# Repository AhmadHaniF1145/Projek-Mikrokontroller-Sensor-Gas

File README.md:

Sistem pendeteksi kebocoran gas adalah sistem elektronik yang dirancang untuk mendeteksi dan memberi peringatan tentang kebocoran gas. Peringatan yang dihasilkan adalah dalam bentuk audio sesuai gas yang dideteksi beserta tingkat bahayanya.

`WORKSHOP MIKROKONTROLLER - PROGRAM STUDI TEKNIK ELEKTRONIKA - POLITEKNIK ELEKTRONIKA NEGERI SURABAYA`

`DOSEN PENGAMPU : Akhmad Hendriawan ST, MT`
`NIP. 197501272002121003`

`TEAM`
| No.  | Nama  | NRP  | Pembagian Tugas  |
| :------------: | :------------: | :------------: | :------------: |
| 1  | Ahmad Hanif Abiyyu Khrisna  | 2122500031  | Pengujian Sistem Pada Software, Pengujian Alat  |
| 2  | Nawfal Ulinnuha F  | 2122500041  | Publikasi melalui Github, Pembelian Hardware  |
| 3  |  Clarrisa Fitria A  | 2122500046  |  Studi Literatur, Pembuatan Audio Project |
| 4  |  Fatimah Azzahro |  2122500047 | Publikasi melalui Github, Pembuatan Audio Project |
| 5  |  Muhammad Ilham K | 2122500052  |  Desain 3D, Proses Perakitan dan Soldering, Proses Pemrograman Arduino |
| 6  | Artur Ferdiansyah  |  2122500059 | Desain Skematik dan PCB Board, Proses Perakitan dan Soldering, Proses Pemrograman Arduino  |

## Daftar Isi
- [Komponen Yang Digunakan](#Komponen-Yang-Digunakan)
- [Konsep Simulasi](#Konsep-Simulasi)
- [Skematik Rangkaian](#Skematik-Rangkaian)
- [Informasi Penempatan Modul dan Komponen](#Informasi-Penempatan-Modul-dan-Komponen)
- [Audio Project](#Audio-Project)
- [Proses Pengerjaan](#Proses-Pengerjaan)
- [Hasil](#Hasil)
- [Cara Penggunaan Alat](#Cara-Penggunaan-Alat)

## Komponen Yang Digunakan
1. Arduino Mega 2560
2. Gas Sensor MQ2
3. OLED 0.96 Inch
4. Push Button
5. LED 3mm
6. SMD LED 1206
7. Speaker/Buzzer
8. Modul amplifier PAM8403
9. IC SPI Flash W25Q32JVSSIQ (4MB)

Dan Beberapa komponen pasif seperti resistor yang salah satunya digunakan sebagai pembatas arus pada LED indikator, dan kapasitor yang digunakan pada blok rangkaian SPI Flash Eksternal yang digunakan sebagai penyimpanan data tambahan.

## Blok Diagram

Prinsip kerja dari sistem pendeteksi kebocoran gas yaitu dimulai dengan sistem pertama kali digunakan dimana sumber daya berasal dari baterai. Ketika tidak terdeteksi kebocoran gas, maka LED hijau akan selalu menyala. Ketika kebocoran gas terdeteksi oleh sensor MQ-2 dengan threshold yang telah disetting oleh push button 1, maka speaker mengeluarkan audio. Untuk informasi threshold yaitu threshold 400 dan 600 masih dalam level siaga dengan indikasi audio "terdeteksi kebocoran gas hati-hati siaga", kemudian threshold 800 sudah dalam level bahaya dengan indikasi audio "bahaya, bahaya, bahaya terdeteksi kebocoran gas". LCD OLED digunakan untuk menampilkan informasi threshold dan banyaknya gas yang terdeteksi. Jika gas yang terdeteksi melebihi threshold, maka speaker mengeluarkan audio dibarengi dengan LED merah yang juga ikut menyala. Untuk mematikan speaker, digunakan push button 2 dan LED hijau kembali menyala yang berarti kondisi sudah diatasi atau sudah aman.

## Konsep Simulasi
Berikut adalah skematik breadboard untuk simulasi menggunakan TinkerCad yang menggunakan Arduino Uno.

https://github.com/AhmadHaniF1145/Projek-Mikrokontroller-Sensor-Gas/assets/168633171/c68b0559-28a6-41bc-bea3-4cfa7fe1158b

## Skematik Rangkaian
Berikut ini adalah hasil skematik rangkaian sistem pendeteksi kebocoran gas menggunakan software KiCad.

Berikut adalah link tutorial dalam pembuatan skematik menggunakan KiCad bisa dilihat pada video [berikut.](https://youtu.be/a5kBzt2_dH4 "berikut.") Untuk semua file yang dibutuhkan terkait skematik rangkaian bisa diakses pada link [berikut.](https://github.com/AhmadHaniF1145/Projek-Mikrokontroller-Sensor-Gas/tree/main/PCB%20Board "berikut.")

## Desain 3D
Berikut ini adalah hasil [desain 3D](https://github.com/AhmadHaniF1145/Projek-Mikrokontroller-Sensor-Gas/tree/main/Desain%203D "Desain 3D") :
1. Desain 3D Casing <br>
<br>
2. Desain 3D Casing + Komponen <br>
<br>
3. Desain 3D PCB dengan Komponen <br>
<br>
4. Desain 3D PCB tanpa Komponen <br>
<br>

Berikut adalah video tutorial pembuatan desain casing menggunakan Autodesk Fusion versi sederhana. Klik link [youtube berikut](https://youtu.be/2gopSfegvmg?si=Se-gvMHZY0zX1dgN "youtube berikut")

Berikut adalah tutorial dalam pembuatan desain PCB menggunakan KiCad pada proyek ini. Bisa klik link [berikut.](https://youtu.be/dg8yomkr-xE "berikut.")

Asset 3D yang sudah jadi dapat di download pada [link Thingiverse berikut](https://www.thingiverse.com/thing:6621092 "link Thingiverse berikut")

## Informasi Penempatan Modul dan Komponen
Tata letak dan informasi terkait penempatan Modul dan Komponen untuk memudahkan pengguna dalam melakukan perakitan <br>
<br>

## Manufacture Drawing untuk Casing
Berikut adalah detail ukuran casing untuk kebutuhan manufaktur
<br>

https://github.com/AhmadHaniF1145/Projek-Mikrokontroller-Sensor-Gas/assets/91182185/3b76fa04-874f-4a73-a389-29a3c4dec217

## Program
Program utama dari projek ini dibagi menjadi dua, yaitu :
- [Arduino dengan C](https://github.com/AhmadHaniF1145/Projek-Mikrokontroller-Sensor-Gas/tree/main/ProgramUtama/Program%20Utama_PlatformIO "Arduino dengan C")
- [Arduino dengan Bare Metal Programming.](https://github.com/AhmadHaniF1145/Projek-Mikrokontroller-Sensor-Gas/tree/main/ProgramUtama/Program%20Utama_Bare%20Metal_PlatformIO "Arduino dengan Bare Metal Programming.")

#### Timer 0
Projek ini memakai Timer 0 untuk memainkan suara yang disimpan pada Flash Memory (dibahas lebih lanjut pada [bagian audio project](## Audio Project "bagian audio project")). Berikut adalah baris kode utama untuk memainkan audio melalui sinyal PWM melalui Timer 0.
`OCR0A = sounddata_length + lastSample - sample;`

#### EEPROM
Alat ini dapat mendeteksi gas dengan Threshold (batas deteksi) yang berbeda sesuai yang diinginkan. Pengguna dapat menekan tombol kiri untuk mengganti mode Threshold. Mode yang diatur akan disimpan pada EEPROM.
`eeprom_write_byte((uint8_t*)0, thresholdIndex);`

Kemudian dibaca menggunakan
`int pilihanLagu = eeprom_read_byte((uint8_t*)0);`

## Audio Project
[Audio Project](https://github.com/AhmadHaniF1145/Projek-Mikrokontroller-Sensor-Gas/tree/main/Audio_Project "Audio Project")
Terdapat 2 mode audio sebagai deteksi adanya kebocoran gas, yaitu :
1. Terdeteksi kebocoran gas hati-hati siaga
2. Bahaya, bahaya, bahaya terdeteksi kebocoran gas

Berikut hasil pembuatan audio dengan hasil editnya menggunakan software Audacity yang kemudian didapatkan file raw yang dibuka melalui software HxD untuk memperoleh datanya dan didapatkan program bahasa C. Program bahasa C tersebut digunakan untuk memrogram Arduino ATMega 2560 agar audio berfungsi. Berikut hasil dokumentasinya  :
1. Terdeteksi kebocoran gas hati-hati siaga <br>
<br>
<br>
<br>
Hasil audio sebelum dan sesudah diedit menggunakan software Audacity [di sini](https://youtu.be/VL2fVMhNUZw "di sini").
2. Bahaya, bahaya, bahaya terdeteksi kebocoran gas <br>
<br>
<br>
<br>
Hasil audio sebelum dan sesudah diedit menggunakan software Audacity [di sini](https://youtu.be/l1GMS38mKNk "di sini").
3. Video Tutorial : Langkah - Langkah Convert Audio Ke Bahasa C

   https://github.com/AhmadHaniF1145/Projek-Mikrokontroller-Sensor-Gas/assets/168683498/8abb6570-371c-4412-ba63-2867d9131914

## Proses Pengerjaan
Berikut dokumentasi pada proses pengerjaan. [Dokumentasi](https://github.com/AhmadHaniF1145/Projek-Mikrokontroller-Sensor-Gas/tree/main/Dokumentasi "Dokumentasi")
1. Studi Literatur <br>
   <br>
2. Pengujian Sistem Pada Software <br>
   <br>
3. Pembuatan Desain Skematik dan PCB Board <br>
   <br>
4. Pembuatan 3D Desain <br>
   <br>
5. Pembelian Hardware <br>
   <br>
6. Proses Perakitan dan Soldering <br>
   <br>
7. Proses Pembuatan Audio <br>
   <br>
8. Proses Pemrograman Arduino <br>
   <br>
9. Pengujian Alat <br>
    <br>
10. Publikasi GitHub <br>
   <br>

## Hasil
1. PCB Print <br>
   <br>
2. 3D Print <br>
   <br>

## Cara Penggunaan Alat

https://github.com/AhmadHaniF1145/Projek-Mikrokontroller-Sensor-Gas/assets/91182185/28567a20-36dd-4a8e-a68d-8d7cb96f8bae

1. Pastikan baterai dalam kondisi penuh kemudian pasang baterai pada tempatnya yaitu di dalam casing. Tutup kemasan dengan benar.
2. Pasang LCD OLED di tempatnya yaitu di luar casing.
3. Nyalakan power switch.
4. Atur threshold sesuai kebutuhan menggunakan push button sebelah kanan. Untuk informasi threshold sebagai berikut.
   Semakin besar nilai threshold maka kebocoran gas yang dideteksi semakin banyak dan bahaya.
   Semakun kecil nilai threshold maka sedikit saja kebocoran gas dapat terdeteksi.
6. Alat sudah siap digunakan untuk mendeteksi kebocoran gas dengan indikator LED hijau menyala jika tidak ada kebocoran gas yang terdeteksi.
7. Apabila sensor telah mendeteksi gas melebihi threshold yang diatur, maka LED warna merah dan audio menyala berulaang-ulang tergantung threshold yang disetting.
   threshold 400 dan 600 dalam level siaga dengan audio "Terdeteksi kebocoran gas hati-hati siaga"
   threshold 800 dalam level bahaya dengan audio "Bahaya, bahaya, bahaya terdeteksi kebocoran gas"
8. Audio bisa dimatikan dengan menekan push button sebelah kiri kemudian LED yang menyala berganti menjadi warna hijau kembali.
Untuk video pengujian alat ini dengan versi HD bisa dilihat pada link [berikut ini](https://youtu.be/NTNdcy7BNHo)

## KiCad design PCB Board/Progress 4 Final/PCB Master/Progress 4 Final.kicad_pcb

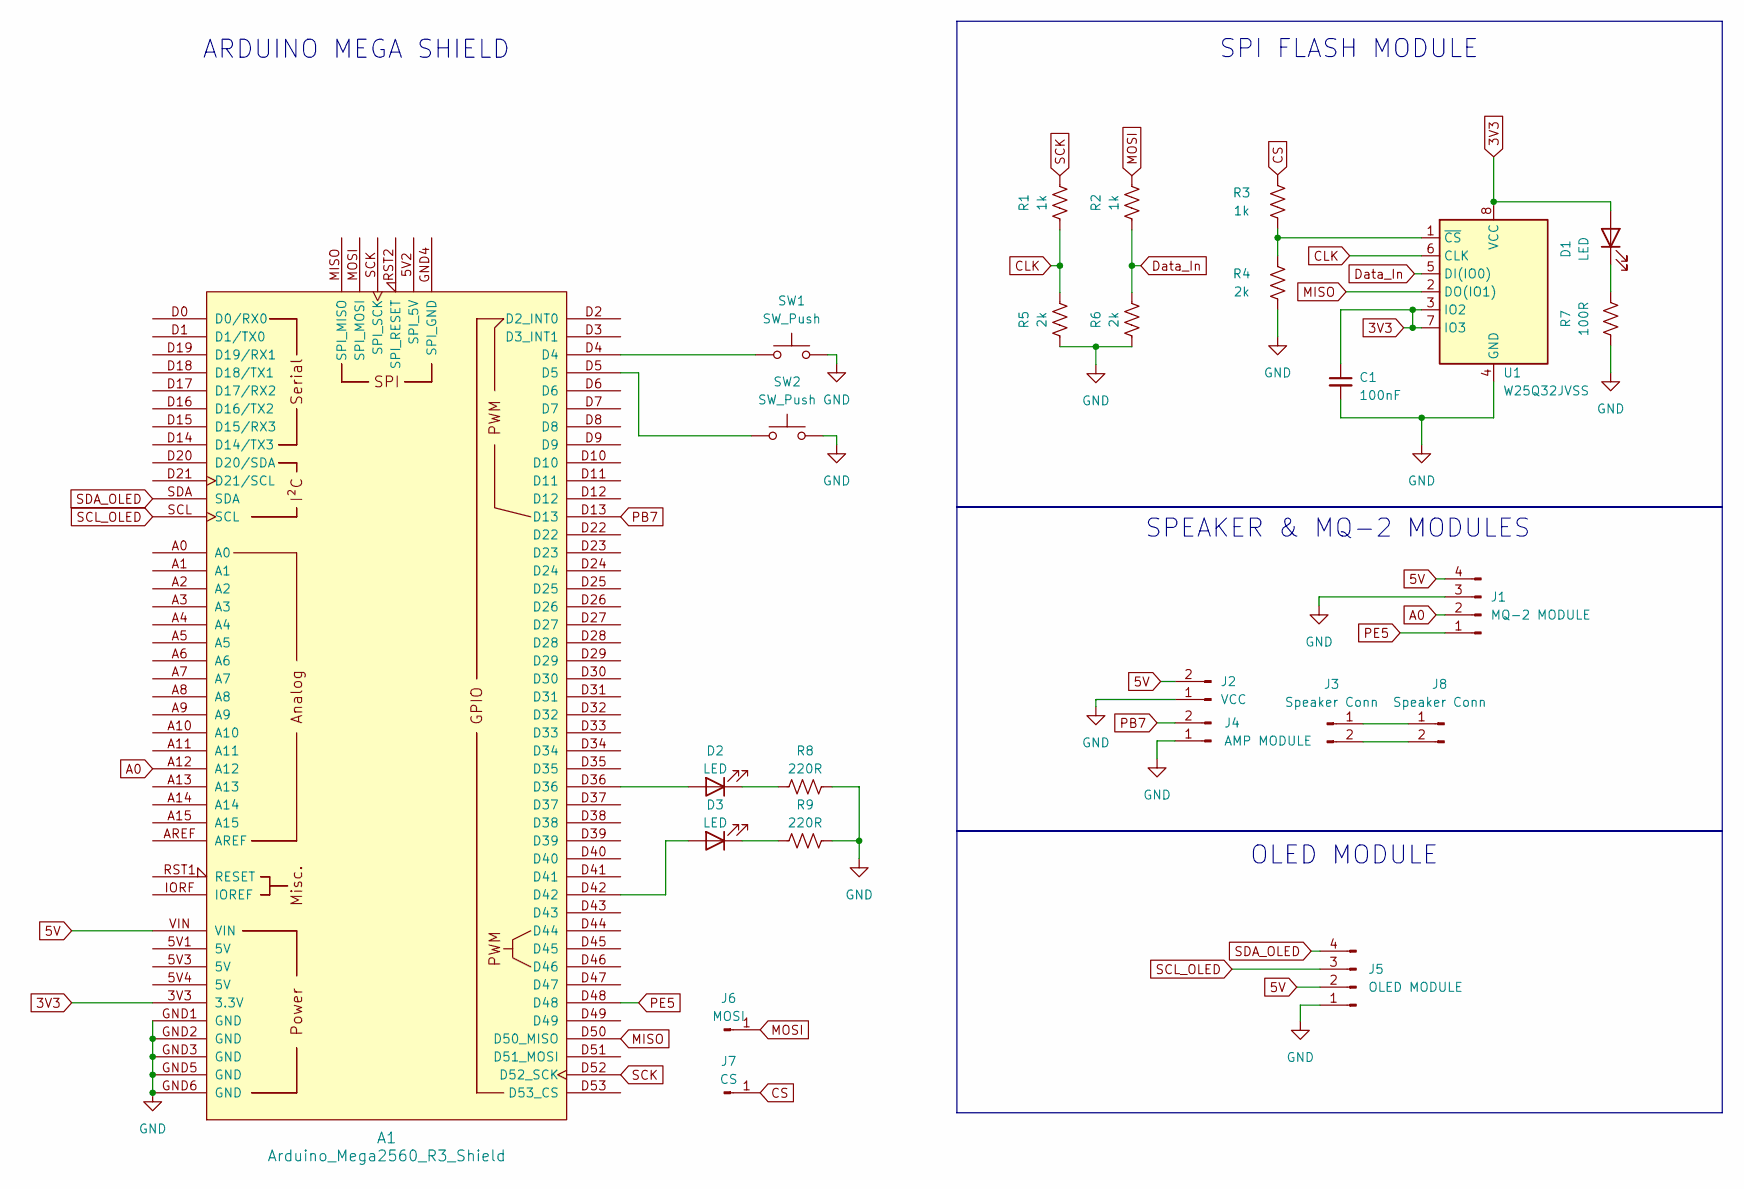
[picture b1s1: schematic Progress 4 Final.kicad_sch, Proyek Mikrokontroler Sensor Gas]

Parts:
A1: Arduino_Mega2560_R3_Shield
C1: 100nF; C_Rect_L7.0mm_W2.5mm_P5.00mm
D1: LED; LED_1206_3216Metric
D2, D3: LED; LED_D5.0mm
J1: MQ-2 MODULE; PinSocket_1x04_P2.54mm_Vertical
J2: VCC; PinSocket_1x02_P2.54mm_Vertical
J3, J8: Speaker Conn; PinSocket_1x02_P2.54mm_Vertical
J4: AMP MODULE; PinSocket_1x02_P2.54mm_Vertical
J5: OLED MODULE; PinSocket_1x04_P2.54mm_Vertical
J6: MOSI; PinHeader_1x01_P2.54mm_Vertical
J7: CS; PinHeader_1x01_P2.54mm_Vertical
R1, R2, R3: 1k; R_1206_3216Metric
R4, R5, R6: 2k; R_1206_3216Metric
R7: 100R; R_1206_3216Metric
R8, R9: 220R; R_Axial_DIN0207_L6.3mm_D2.5mm_P10.16mm_Horizontal
SW1, SW2: SW_Push; SW_PUSH_6mm_H8mm
U1: W25Q32JVSS; SOP-8_5.28x5.23mm_P1.27mm

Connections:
3V3: A1.3V3 (3.3V), C1.1, D1.2 (A), U1.3 (IO2), U1.7 (IO3), U1.8 (VCC)
5V: A1.VIN, J1.4, J2.2, J5.2
A0: A1.A12, J1.2
CLK: R1.2, R5.1, U1.6 (CLK)
CS: J7.1, R3.2
Data_In: R2.2, R6.1, U1.5 (DI(IO0))
GND: A1.GND1 (GND), A1.GND2 (GND), A1.GND3 (GND), A1.GND5 (GND), A1.GND6 (GND), C1.2, J1.3, J2.1, J4.1, J5.1, R4.1, R5.2, R6.2, R7.1, R8.2, R9.2, SW1.1, SW2.1, U1.4 (GND)
MISO: A1.D50 (D50_MISO), U1.2 (DO(IO1))
MOSI: J6.1, R2.1
unnamed: A1.D4, SW1.2
unnamed: A1.D5, SW2.2
unnamed: D1.1 (K), R7.2
unnamed: A1.D36, D2.2 (A)
unnamed: D2.1 (K), R8.1
unnamed: A1.D42, D3.2 (A)
unnamed: D3.1 (K), R9.1
unnamed: J3.1, J8.1
unnamed: J3.2, J8.2
unnamed: R3.1, R4.2, U1.1 (~CS)
PB7: A1.D13, J4.2
PE5: A1.D48, J1.1
SCK: A1.D52 (D52_SCK), R1.1
SCL_OLED: A1.SCL, J5.3
SDA_OLED: A1.SDA, J5.4

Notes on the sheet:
SPI FLASH MODULE
OLED MODULE
SPEAKER & MQ-2 MODULES
ARDUINO MEGA SHIELD

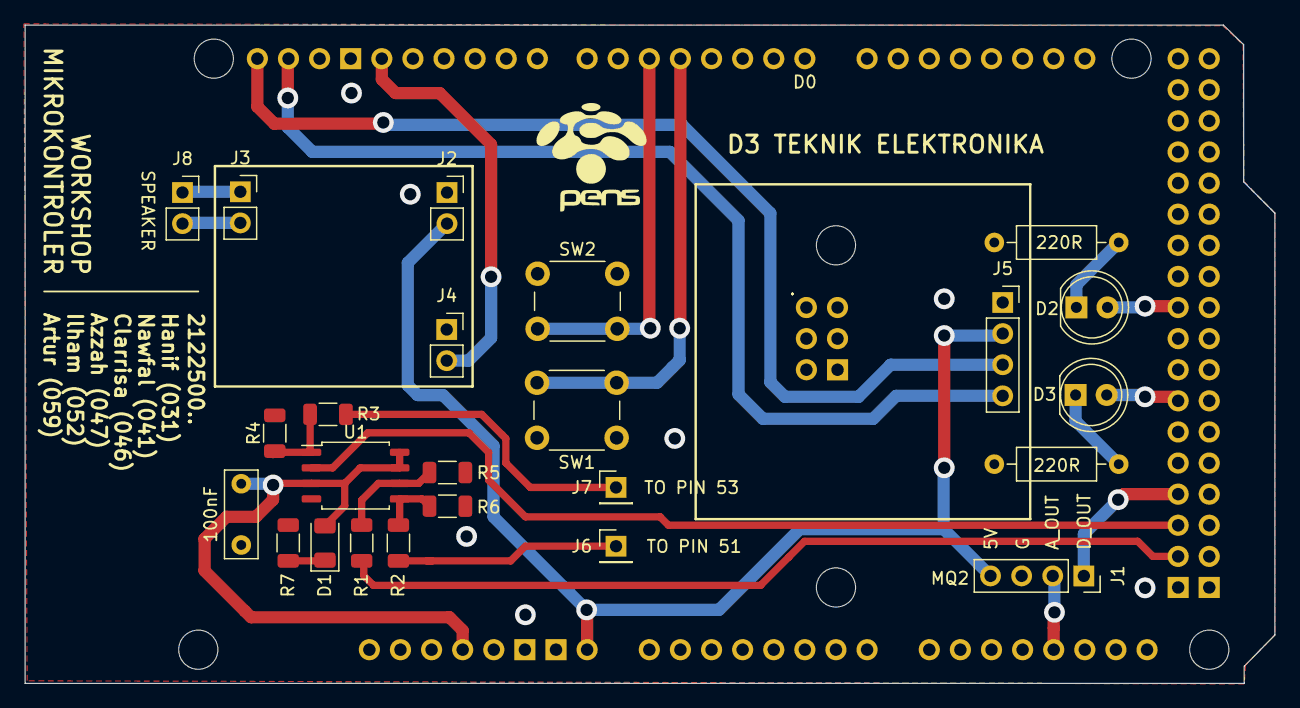
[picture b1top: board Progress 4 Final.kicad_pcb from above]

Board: 2 copper layers, 102.0 x 53.8 mm, 25 parts (0 on the bottom side), 24 nets.

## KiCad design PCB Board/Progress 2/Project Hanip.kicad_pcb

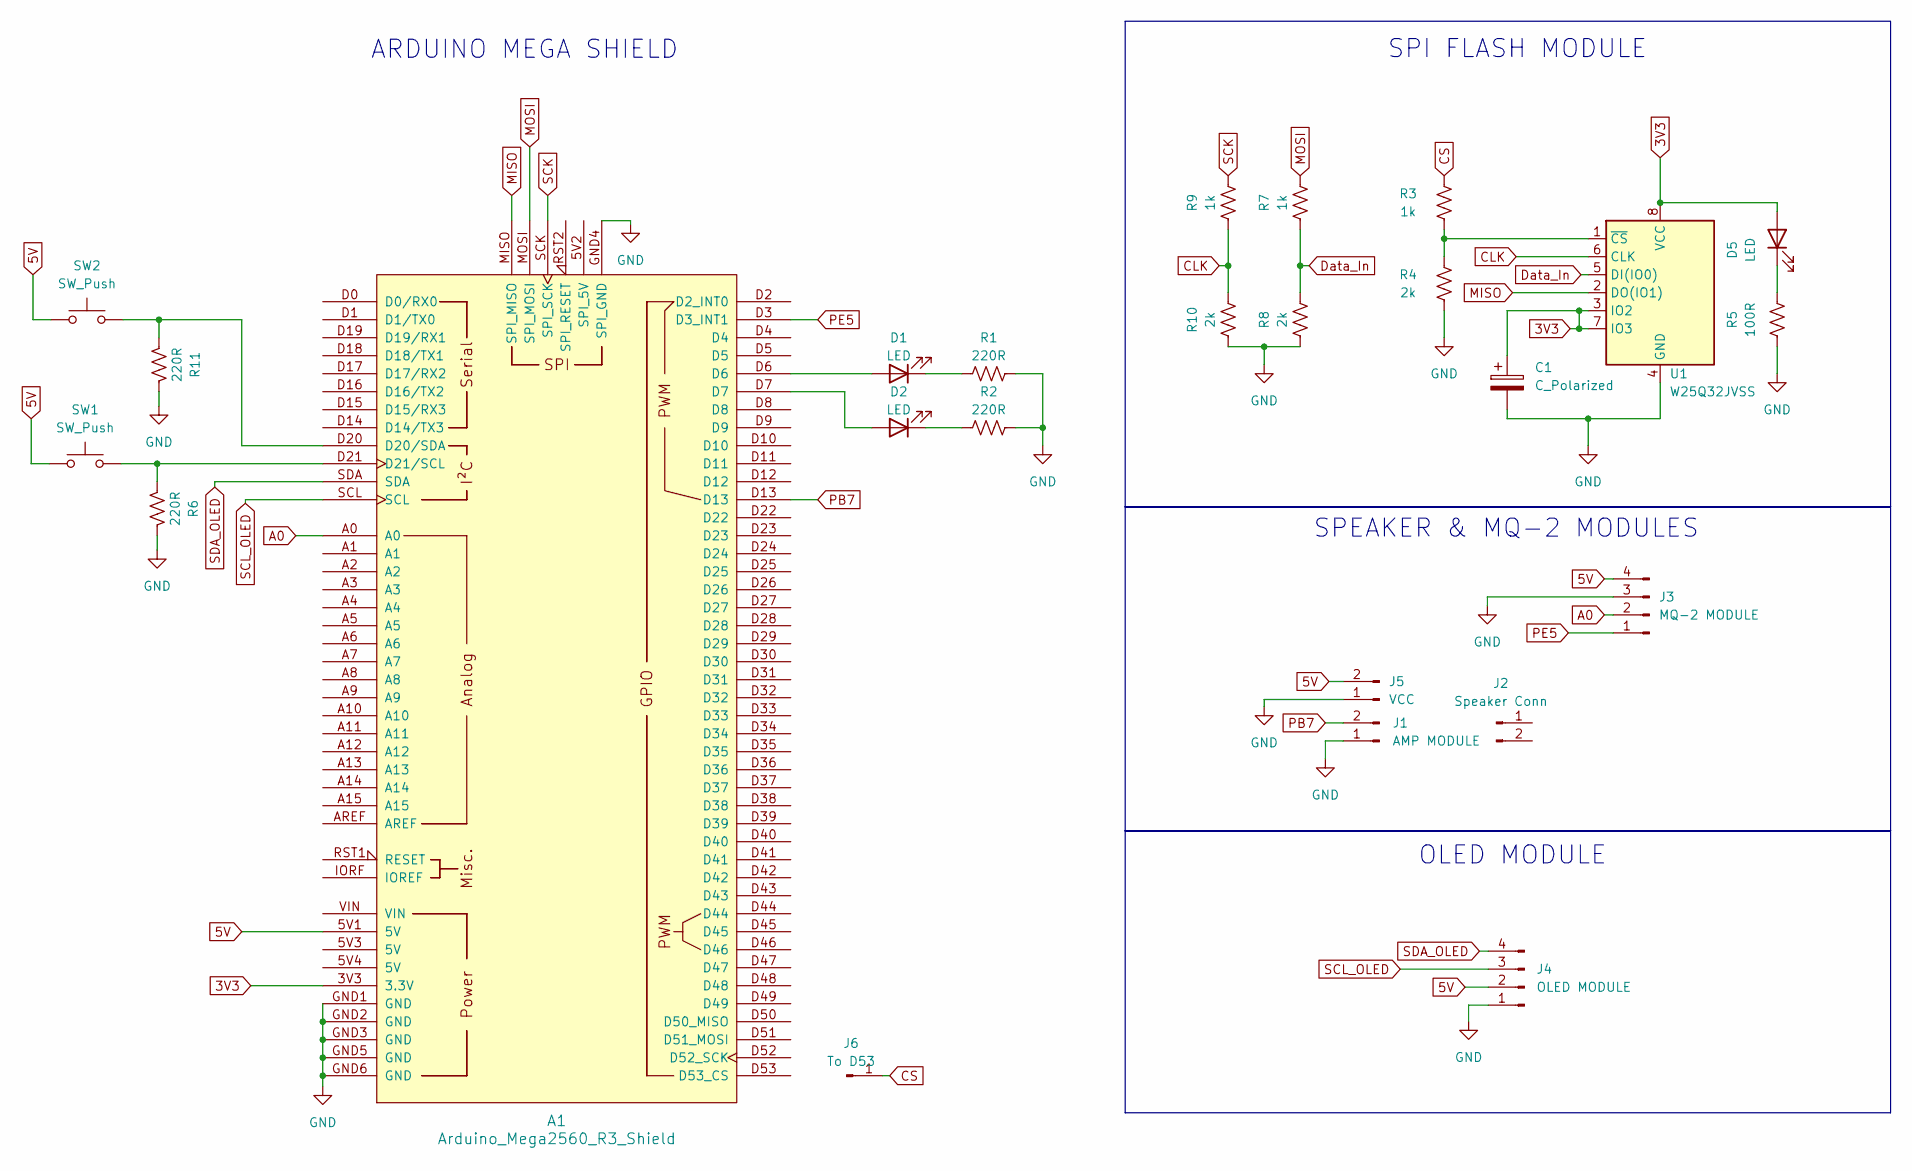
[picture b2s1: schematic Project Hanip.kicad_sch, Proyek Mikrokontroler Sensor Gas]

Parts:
A1: Arduino_Mega2560_R3_Shield
C1: C_Polarized; CP_Radial_D6.3mm_P2.50mm
D1, D2: LED; LED_D5.0mm
D5: LED; LED_1206_3216Metric
J1: AMP MODULE; PinSocket_1x02_P2.54mm_Vertical
J2: Speaker Conn; PinSocket_1x02_P2.54mm_Vertical
J3: MQ-2 MODULE; PinSocket_1x04_P2.54mm_Vertical
J4: OLED MODULE; PinSocket_1x04_P2.54mm_Vertical
J5: VCC; PinSocket_1x02_P2.54mm_Vertical
J6: To D53; PinSocket_1x01_P2.54mm_Vertical
R1, R2, R6, R11: 220R; R_Axial_DIN0207_L6.3mm_D2.5mm_P10.16mm_Horizontal
R3, R7, R9: 1k; R_1206_3216Metric
R4, R8, R10: 2k; R_1206_3216Metric
R5: 100R; R_1206_3216Metric
SW1, SW2: SW_Push; SW_PUSH_6mm_H8mm
U1: W25Q32JVSS; SOP-8_5.28x5.23mm_P1.27mm

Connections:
3V3: A1.3V3 (3.3V), C1.1, D5.2 (A), U1.3 (IO2), U1.7 (IO3), U1.8 (VCC)
5V: A1.5V1 (5V), J3.4, J4.2, J5.2, SW1.2, SW2.2
A0: A1.A0, J3.2
CLK: R9.2, R10.1, U1.6 (CLK)
CS: J6.1, R3.2
Data_In: R7.2, R8.1, U1.5 (DI(IO0))
GND: A1.GND1 (GND), A1.GND2 (GND), A1.GND3 (GND), A1.GND4 (SPI_GND), A1.GND5 (GND), A1.GND6 (GND), C1.2, J1.1, J3.3, J4.1, J5.1, R1.2, R2.2, R4.1, R5.1, R6.1, R8.2, R10.2, R11.1, U1.4 (GND)
MISO: A1.MISO (SPI_MISO), U1.2 (DO(IO1))
MOSI: A1.MOSI (SPI_MOSI), R7.1
unnamed: A1.D20 (D20/SDA), R11.2, SW2.1
unnamed: A1.D21 (D21/SCL), R6.2, SW1.1
unnamed: A1.D6, D1.2 (A)
unnamed: D1.1 (K), R1.1
unnamed: A1.D7, D2.2 (A)
unnamed: D2.1 (K), R2.1
unnamed: D5.1 (K), R5.2
unnamed: R3.1, R4.2, U1.1 (~CS)
PB7: A1.D13, J1.2
PE5: A1.D3 (D3_INT1), J3.1
SCK: A1.SCK (SPI_SCK), R9.1
SCL_OLED: A1.SCL, J4.3
SDA_OLED: A1.SDA, J4.4

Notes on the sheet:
SPI FLASH MODULE
OLED MODULE
SPEAKER & MQ-2 MODULES
ARDUINO MEGA SHIELD

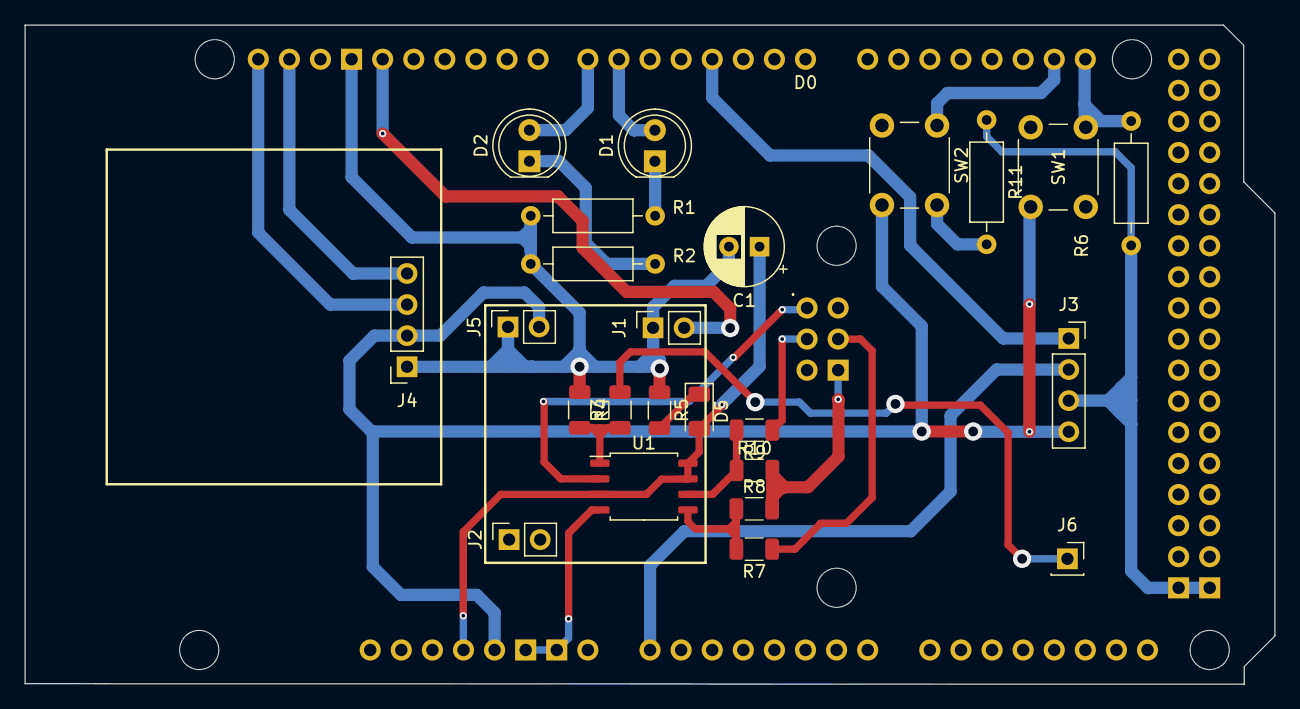
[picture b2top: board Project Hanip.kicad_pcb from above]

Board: 2 copper layers, 102.1 x 53.9 mm, 25 parts (0 on the bottom side), 22 nets.

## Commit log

2024-05-06 nambah file arduino
2024-05-06 artur
2024-05-06 Add files via upload
    Studi Literatur (Clarrisa)
2024-05-06 Datsheet MQ2
    Sensor Mq2(Clarrisa)
2024-05-07 Create Tes
2024-05-07 upload file 3D
2024-05-07 organisasi folder
2024-05-12 Progress 2
2024-05-12 update progres 3D dengan Fusion
2024-05-13 nambah asset gambar
2024-05-13 ganti gambar banner
2024-05-13 edit README
2024-05-13 menambah gambar skematik kicad
2024-05-14 menambah screenshot 3D
2024-05-14 nambah file 3D
2024-05-14 Program
2024-05-14 Readme update
2024-05-17 Schematic PCB
2024-05-17 PCB Board Design
2024-05-17 Asset Folder
2024-05-17 new audio
2024-05-17 3D Design PCB
2024-05-17 PCB Schematic Update
2024-05-17 3D PCB File Design
2024-05-17 Schematic Update
2024-05-17 PCB Wizard Update
2024-05-17 PCB Top
2024-05-17 PCB Silk Screen Update
2024-05-17 Audio Folder
2024-05-17 PCB Bottom Silk Screen Update
2024-05-17 PCB Bottom
2024-05-17 Progress 4 PCB
2024-05-17 update skematik PCB
2024-05-19 update program
2024-05-19 audio convert
2024-05-19 new file
2024-05-20 update file 3D
2024-05-21 update program ino
2024-05-23 menambah program simulasi audio
2024-05-24 Memulai pembuatan program utama
2024-05-24 menyesuaikan program utama
2024-05-24 Add bare metal programming
2024-05-24 Sedikit perubahan pada kode bare metal
2024-05-25 Rearrange Folder
2024-05-25 Rearrange File and Folder
2024-05-27 Nambah library OLED
2024-05-27 menyempurnakan OLED
2024-05-27 menambahkan library pinChangeInterrupt
2024-05-27 Menambahkan fungsi StopPlayback
2024-05-27 Nambah asset ukuran
2024-05-28 update dokumentasi
2024-05-28 update pcb
2024-05-28 update program utama
2024-05-28 update pin
2024-05-28 Program suara sempurna
2024-05-28 update studi
2024-05-28 PCB Warna Warni
2024-05-31 menambag looping suara
2024-05-31 menambah variable threshold
2024-05-31 program versi 1 selesai
2024-06-03 menambahkan fungsi EEPROM
2024-06-03 menambahkan fungsi ADC pada bare Metal
2024-06-03 menyempurnakan fungsi ADC pada bare Metal
2024-06-03 menyempurnakan Bare Metal
2024-06-03 menyempurnakan eeprom
2024-06-04 New Readme
